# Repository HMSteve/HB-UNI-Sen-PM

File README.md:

# HB-UNI-Sen-PM

Eine AskSinPP-Implementierung eines Feinstaubsensors fuer den Aussenbereich mit dem PM-Sensor SPS30 sowie dem Feuchtesensor SHT31 von Sensirion. Das Geraet kann regulaer in eine Homematic-Umgebung eingebunden werden und liefert folgende Messwerte:

- Feinstaubkonzentrationen PM1, PM2.5, PM4 und PM10 im µg/m³
- Partikelanzahlen je cm³ fuer Partikelgroessen <0.5µm, <1µm, <2.5µm, <4µm und <10µm
- Temperatur
- relative Luftfeuchte

## Platinen

Schaltplaene, Bestueckungsplaene, Gerber Files sowie Eagle Files finden sich [hier](https://github.com/HMSteve/HB-UNI-Sen-PM/tree/main/PCB).

Hauptplatine

Hauptplatine mit SHT31-Platine

Beide Platinen mit SPS30

### Bestueckung

Die Bestueckung der Hauptplatine ist unkritisch und kann per Hand erfolgen, es werden Bauformen 0805 oder groesser genutzt.

Bei der Feuchtesensorplatine ist der SHT31 zuerst zu bestuecken. Grundsaetzlich ist Handloetung unter guter Lupe oder Mikroskop moeglich, vorteilhaft ist jedoch der Auftrag von Lotpaste mittels Schablone und Loetung mit Hitze, bspw. Heissluft, von unten durch die Platine. Bei diesem Verfahren ist keine 100% exakte Positionierung des Bauteils noetig, da es bei korrekt dosierter Lotpaste nach deren Aufschmelzen auf Grund der Oberflaechenspannung auf dem flüssigen Lot von selbst in die korrekte Position schwimmt. Lupe oder Mikroskop zur Kontrolle der Loetstellen von der Seite sollte man nutzen. Anschliessend wird die Schutzkappe in die vorgesehenen Loecher eingesteckt und haelt ohne Klebstoffe etc.
Die beiden Platinen sollten erst ganz zum Schluss, nach Test und ggf. nach Waschen der Hauptplatine, zusammengesteckt und verloetet werden. Der SHT31 darf weder Waschfluessigkeit wie Isopropanol noch deren Daempfen ausgesetzt werden. Anderenfalls ist mit einer (ohne langwieriges Backen) irreversiblen Fehlmessung der Luftfeuchte zu rechnen.

Der Loetjumper ist gemaess Datenblatt des SHT31 unbedingt nach Masse zu schliessen, um unerwuenschte Effekte wie Aussetzer bei hoher Luftfeuchte zu vermeiden.

ACHTUNG: Version 2 der Hauptplatine besitzt einen fehlerhaften Aufdruck der Betriebsspannungspolaritaet. Dies unbedingt beachten. +5V sind an den Pin zum Platinenrand anzuschliessen, Masse an den Pin zur Platinenmitte. Auch nur kurze Verpolung kann bereits zur Zerstoerung des Elkos vor dem LDO und ggf. weiterer Bauteile fuehren.

## Software

### Addon zur Geraeteunterstuetzung

Sofern noch nicht vorhanden oder nicht aktuell, ist das [Addon](https://github.com/HMSteve/SG-HB-Devices-Addon/raw/master/CCU_RM/sg-hb-devices-addon.tgz) auf der CCU zu installieren. Der Sensor benoetigt mindestens Version 1.61.

### Firmware

Es wird ein ATMega328p mit Quarz verwendet. Deshalb kann bei Nutzung der Arduino IDE der Arduino Pro Mini ausgewaehlt und der Standard-Bootlader geflashed werden.

Um die Firmware zu kompilieren, muessen sich die .ino sowie die .h Dateien im gleichen Verzeichnis befinden, das ./sensors-Verzeichnis darunter. Zudem muss eine Reihe von Bibliotheken ueber den Library Manager eingebunden werden:
- AskSinPP
- EnableInterrupt
- LowPower
- SparkFun SCD30 Arduino Library
- Sensirion-sps30
-

Anschliessend sollte die Firmware problemlos kompilierbar und das Device nach dem Flashen anlernbar sein. Da der Anlerntaster zwecks Wetterschutz nicht von ausserhalb des Gehaeuses zugaenglich ist, muss das Anlernen vor dem Zusammenbau erfolgen.

## Gehaeuse

Das auessere Gehaeuse orientiert sich an einem aehnlichen [Projekt](https://www.thingiverse.com/thing:2821592), verwendet jedoch nur die mittleren Ringe des Stevenson Screen. Die uebrigen Dateien wurden von mir dazu passend erstellt. Alle STLs finden sich [hier](https://github.com/HMSteve/HB-UNI-Sen-PM/tree/main/3D_Druck).
Neben den 3D-Druckteilen wird folgendes Material benoetigt:

- je vier Einschmelzmuttern M3 und M8 fuer den Deckel
- ein O-Ring 5mm x 1, moeglich ist auch 6mm x 1.5 oder aehnlich, zum Abdichten der Sensirion-SF2-Filterkappe ueber dem SHT31 gegen das innere Gehaeuse
- vier Schrauben M3 x 10, Edelstahl oder Messing, zum Montieren des inneren Gehaeuses am Deckel
- EPDM-Dichtschnur 3mm zum Abdichten des inneren Gehaeuses gegen den Deckel
- vier Gewindestange M8 zzgl. vier Muttern M8 zum Zusammenbau von Deckel, Zwischenringen und Haltewinkel, Edelstahl oder Messing
- eine PG-Verschraubung M12 zur Einfuehrung der Stromversorgung
- etwas elastisches Material wie PE-Schaum zwischen Deckel und Sensor sowie Platine, um diese mit etwas Druck gegen die Gehaeuseunterseite beim Zusammenschrauben zu fixieren

Ein paar Fotos vom Aufbau:

Einschmelzmuttern im Deckel

Deckel und Innengehaeuse vor Montage

Deckel und Innengehaeuse montiert

Blick von unten ins komplett montierte Gehaeuse

Hinweis: Vor Einschieben der Platine ins Gehaeuse ist der O-Ring ueber der entsprechenden Gehaeuseoeffnung zu plazieren und dann die Platine sehr vorsichtig einzuschieben, um ein Verrutschen des O-Rings zu vermeiden. An der Unterseite des Deckels sollten zwei Stuecke flexiblem Kunststoffes, z.B. PE-Schaum zu Verpackungszwecken, mit doppelseitigem Klebeband fixiert werden. Diese muessen hoeher als der Auflagerand fuer das Innengehaeuse sein, um beim Zusammenschrauben der Gehaeuseteile Druck auf SPS30 und Platine auszuueben, damit der SPS30 auf den Luftoeffnungen fest aufliegt und der SHT31 auf dem O-Ring. Zusaetzlicher Wetterschutz der Luftoeffnungen kann durch Aufschieben eines Stuecks Schlauch mit 11mm Innendurchmesser erreicht werden. Diese [Schlauchstuecken](https://github.com/HMSteve/HB-UNI-Sen-PM/blob/main/3D_Druck/LuftSchlauch.stl) koennen auch aus TPU gedruckt werden.
Die uebrigen Druckteile sollten aus hinreichend wetterfestem Kunststoff wie PETG oder ASA gedruckt werden.

## Bedienung und Funktion

Das Geraet besitzt drei wesentliche Konfigurationsparameter, die Messdauer und das Sendeintervall sowie das Luftfeuchtelimit. Liegt die relative Luftfeuchte zu Beginn eines Messzyklus im mit dem Luftfeuchtelimit vorgegebenen Bereich (laut Datenblatt sind fuer den SPS30 max. 95% zulaessig), wird der SPS30 gestartet und fuer die Messdauer ohne Auslesen von Messwerten zwecks Stabilisierung betrieben. Anschliessend wird ueber den Zeitraum der Messdauer sekuendlich ein Messdatensatz vom SPS30 geliefert. Ueber diese Messdatensaetze wird der Mittelwert als Ausgabewert des Geraetes gebildet. Anschliessend wird der SPS30 abgeschaltet, das Geraet wartet bis zum Ende des Sendeintervalls und startet den naechsten Messzyklus. Details zu diesem Vorgehen sind [hier](https://sensirion.com/media/documents/188A2C3C/6166F165/Sensirion_Particulate_Matter_AppNotes_SPS30_Low_Power_Operation_D1.pdf) nachzulesen.
Liegt zu Beginn des Messzyklus die relative Feuchte ueber dem Limit, erfolgt keine Feinstaubmessung und in der WebUI bleiben bei Aktualisierung von Temperatur und Feuchte die Feinstaubwerte unveraendert. Dies wird durch den Hinweis auf nicht aktuelle Feinstaubwerte kenntlich gemacht.

Ein Sendeintervall kleiner als 2x Messdauer ist mithin nicht sinnvoll. Solche Einstellungen fuehren zu einem Sendeintervall etwas oberhalb von 2x Messdauer unabhaengig von der Einstellung des Sendeintervalls.

Der Sensor sollte dauerhaft mit 5V versorgt werden. Batterieversorgung ist auf Grund der relative hohen Stromaufnahme des SPS30 nicht sinnvoll. Ein hoeherfrequentes Ein- und Ausschalten der Betriebsspannung ist nicht sinnvoll, da das Geraet alle 5 Tage eine Luefterreinigung des SPS30 durchfuehrt. Zur Minimierung des Stromverbrauchs und insb. Vermeidung von Eigenerwaermung im Gehaeuse wird der ATMega nach jedem Messzyklus in den sleep mode versetzt. Geaenderte Konfigurationsparameter werden deshalb erst mit dem naechsten Messzyklus an das Geraet uebertragen.

Die Konfigurationsseite:

Die Messwerte werden dann so angezeigt:

Dabei ist zu beachten, dass die Werte kumulativ sind. PM10 enthaelt also alle Partikel <=10 µm und schliesst damit die Werte der kleineren Partikelgroessen mit ein.

## Disclaimer

Die Nutzung der hier veroeffentlichten Inhalte erfolgt vollstaendig auf eigenes Risiko und ohne jede Gewaehr.

## Lizenz

**Creative Commons BY-NC-SA**<br>
Give Credit, NonCommercial, ShareAlike

<br />This work is licensed under a <a rel="license" href="http://creativecommons.org/licenses/by-nc-sa/4.0/">Creative Commons Attribution-NonCommercial-ShareAlike 4.0 International License</a>.

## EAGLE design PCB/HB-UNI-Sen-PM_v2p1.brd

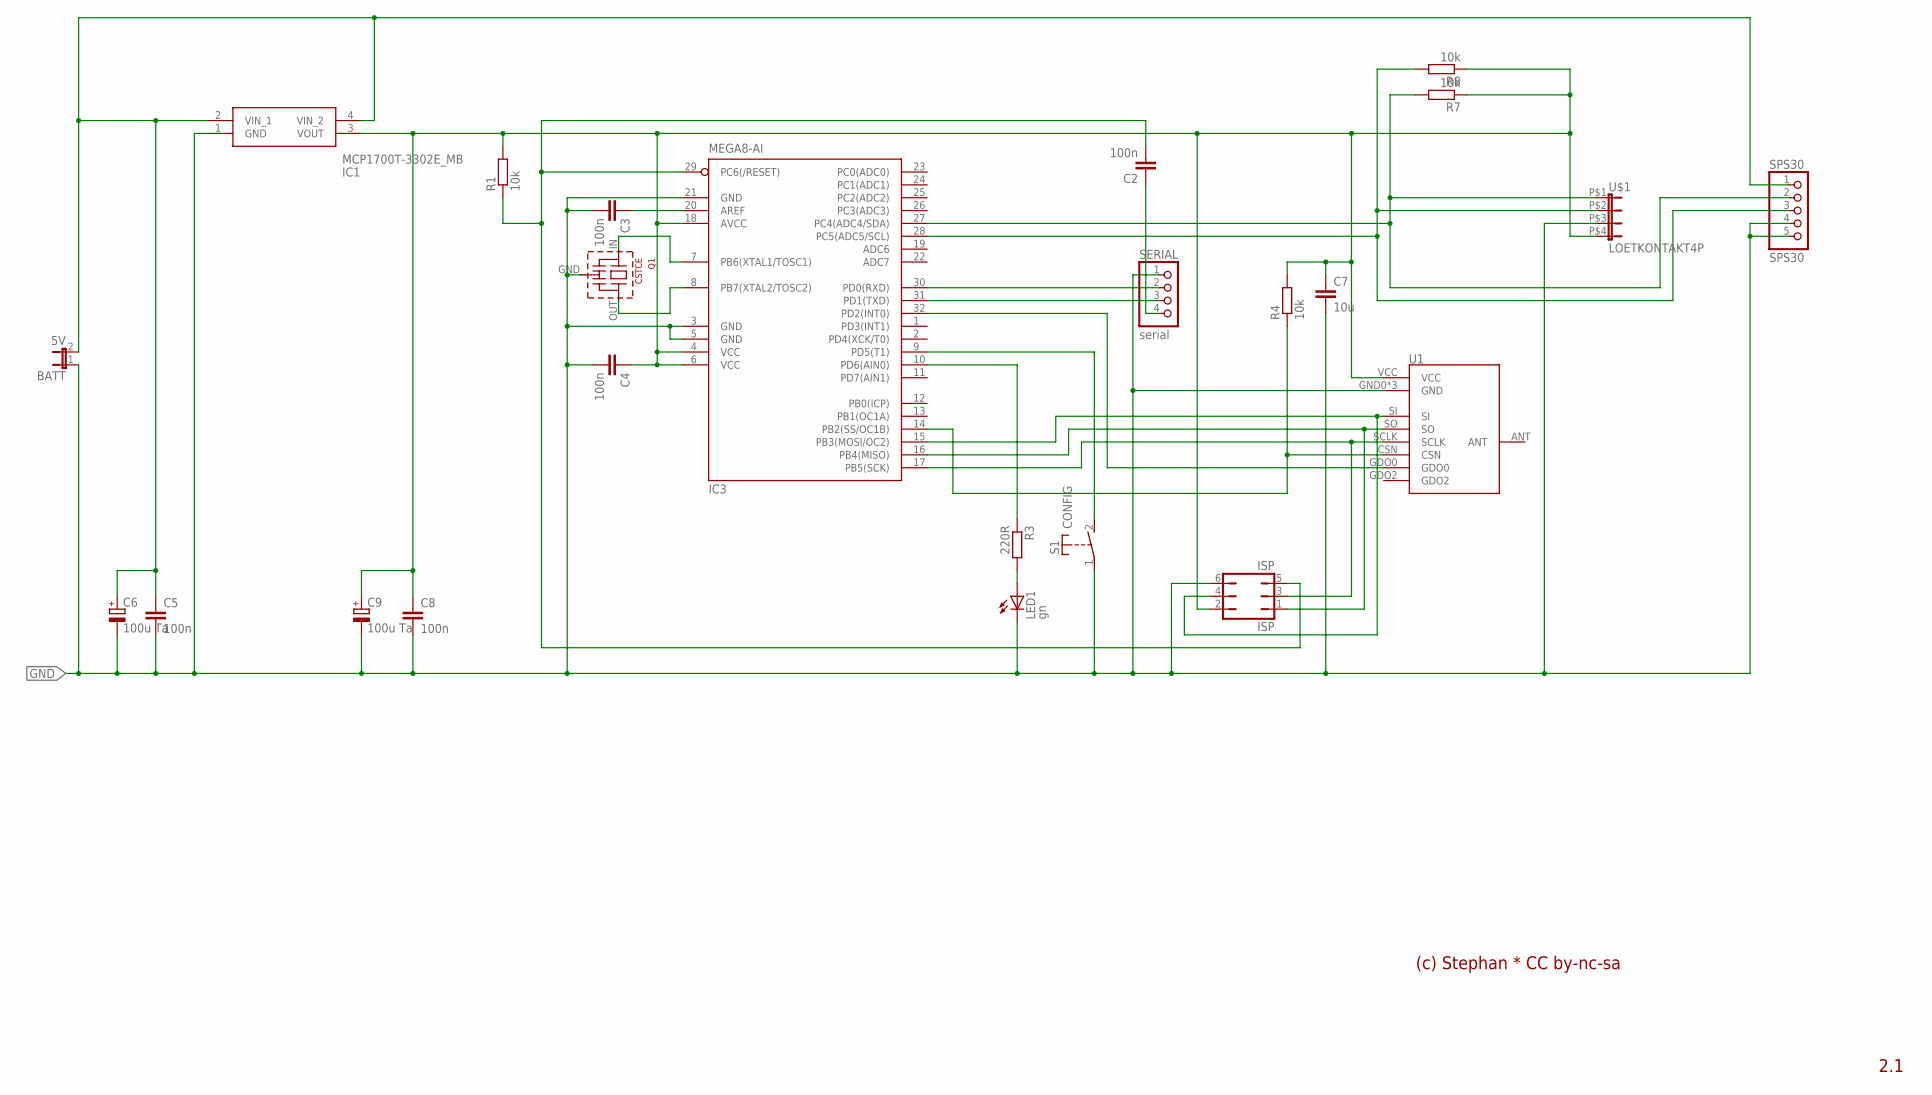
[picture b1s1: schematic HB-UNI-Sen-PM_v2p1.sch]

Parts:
BATT: 5V; JP1
C2, C3, C4, C5, C8: 100n; C0805K
C6, C9: 100u Ta; SANYO-OSCON_SMD_C6
C7: 10u; C0805K
IC1: MCP1700T-3302E_MB; MCP1700T-3302E/MB
IC3: MEGA8-AI; TQFP32-08
ISP: ISP; JP3Q
LED1: gn; CHIPLED_0805
Q1: CSTCE
R1, R4, R7, R8: 10k; R0805W
R3: 220R; R0805W
S1: CONFIG; SMDSWITCH6X4
SERIAL: serial; 1X04
SPS30: SPS30; 1X05
U1: CC1101SMD; CC1101-SMD
U$1: LOETKONTAKT4P

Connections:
3V3: C4.1, C7.1, C8.1, C9.+, IC1.3 (VOUT), IC3.4 (VCC), IC3.6 (VCC), IC3.18 (AVCC), ISP.2, R1.2, R4.2, R7.1, R8.1, U1.VCC, U$1.P$4 (4)
5V: BATT.2, C5.1, C6.+, IC1.2 (VIN_1), IC1.4 (VIN_2), SPS30.1
AREF: C3.1, IC3.20 (AREF)
CSN: IC3.14 (PB2(SS/OC1B)), R4.1, U1.CSN
DTR: C2.1, SERIAL.4
GDO0: IC3.32 (PD2(INT0)), U1.GDO0
GND: BATT.1, C3.2, C4.2, C5.2, C6.-, C7.2, C8.2, C9.-, IC1.1 (GND), IC3.3 (GND), IC3.5 (GND), IC3.21 (GND), ISP.6, LED1.C, Q1.GND, S1.1, SERIAL.1, SPS30.4, SPS30.5, U1.GND0 (GND), U1.GND1 (GND), U1.GND2 (GND), U$1.P$3 (3)
LED1: LED1.A, R3.2
MISO: IC3.16 (PB4(MISO)), ISP.1, U1.SO
MOSI: IC3.15 (PB3(MOSI/OC2)), ISP.4, U1.SI
PD5: IC3.9 (PD5(T1)), S1.2 (S)
PD6: IC3.10 (PD6(AIN0)), R3.1
RESET: C2.2, IC3.29 (PC6(/RESET)), ISP.5, R1.1
RXD: IC3.30 (PD0(RXD)), SERIAL.2
SCL: IC3.28 (PC5(ADC5/SCL)), R8.2, SPS30.3, U$1.P$2 (2)
SCLK: IC3.17 (PB5(SCK)), ISP.3, U1.SCLK
SDA: IC3.27 (PC4(ADC4/SDA)), R7.2, SPS30.2, U$1.P$1 (1)
TXD: IC3.31 (PD1(TXD)), SERIAL.3
XTAL1: IC3.7 (PB6(XTAL1/TOSC1)), Q1.IN
XTAL2: IC3.8 (PB7(XTAL2/TOSC2)), Q1.OUT

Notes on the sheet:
2.1
(c) Stephan * CC by-nc-sa

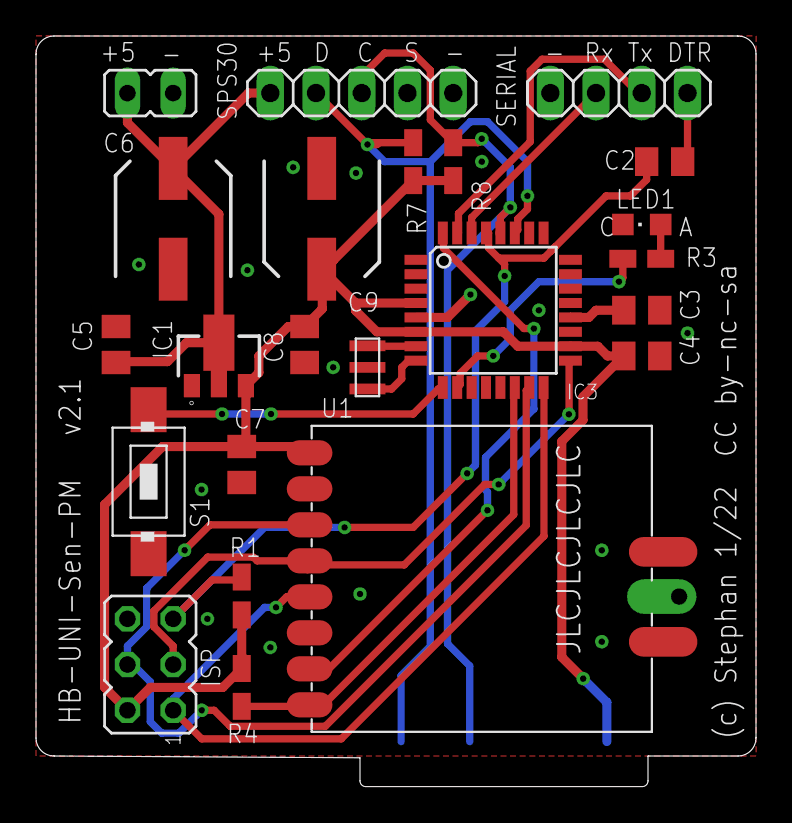
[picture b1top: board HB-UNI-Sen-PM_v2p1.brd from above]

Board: 2 copper layers, 40.0 x 41.7 mm, 24 parts (1 on the bottom side), 20 nets.

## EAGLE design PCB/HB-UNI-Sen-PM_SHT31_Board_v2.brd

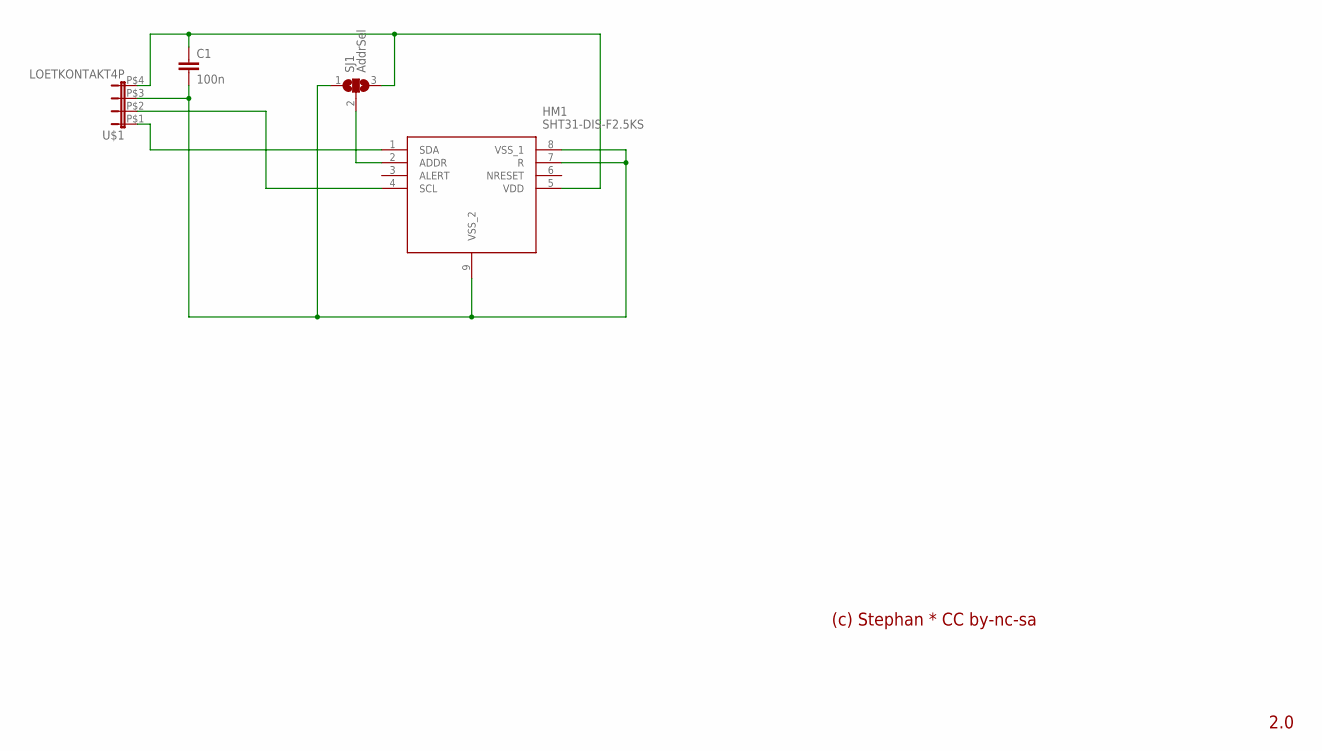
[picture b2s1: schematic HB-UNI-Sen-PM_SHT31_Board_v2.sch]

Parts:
C1: 100n; C0603K
HM1: SHT31-DIS-F2.5KS; SON50P250X250X90-9N
SJ1: AddrSel; SJ_2
U$1: LOETKONTAKT4P

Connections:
3V3: C1.1, HM1.5 (VDD), SJ1.3, U$1.P$4 (4)
ADDR: HM1.2 (ADDR), SJ1.2
GND: C1.2, HM1.7 (R), HM1.8 (VSS_1), HM1.9 (VSS_2), SJ1.1, U$1.P$3 (3)
SCL: HM1.4 (SCL), U$1.P$2 (2)
SDA: HM1.1 (SDA), U$1.P$1 (1)

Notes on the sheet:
(c) Stephan * CC by-nc-sa
2.0

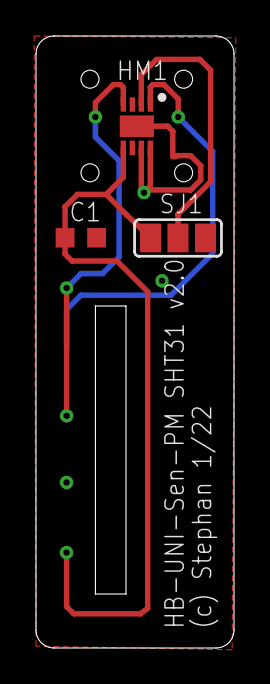
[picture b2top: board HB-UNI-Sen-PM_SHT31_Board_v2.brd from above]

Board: 2 copper layers, 11.0 x 34.0 mm, 4 parts (1 on the bottom side), 5 nets.

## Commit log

2021-12-29 pcb added
2022-01-27 pcb silkscreen corrected in v2.1, first working version of software
2022-01-30 humindity threshold and fan cleaning added
2022-02-04 fan cleaning and sampling period added
2022-02-05 stls added
2022-02-05 images added
2022-02-08 readme updated, datasheets added
2022-07-30 config param humidityLimit added

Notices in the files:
PCB/HB-UNI-Sen-PM_v2p1.brd:
(c) Stephan 1/22  CC by-nc-sa
parts and their libraries:
modules: Released under the Creative Commons Attribution 4.0 International License: http://creativecommons.org/licenses/by/4.0
